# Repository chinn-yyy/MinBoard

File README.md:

# MinBoard
Ever wanted to record score for a board game and thought this pen and paper is boring. Well, I introduce you to the MinBoard, the "first" ever mini scoreboard you can take wherever you want. It features two "point" squares and one "time" square that can display how long is left and who is winning.

This design includes 3 buttons, one to add a point to HOME, one to add a point to AWAY, and 1 to reset the SCORE and TIME. Also, there is a push-dial you can adjust the TIME with, spin to change and press to confirm/start.
Any questions, bugs, inquiries, suggestions, etc. DM me on slack "@chinnyyy.".

**Photos:**

CAD:

SCHEMATIC:

PCB:

FULLY ASSEMBLED:

(not yet)

made/designed by chinnyyy.

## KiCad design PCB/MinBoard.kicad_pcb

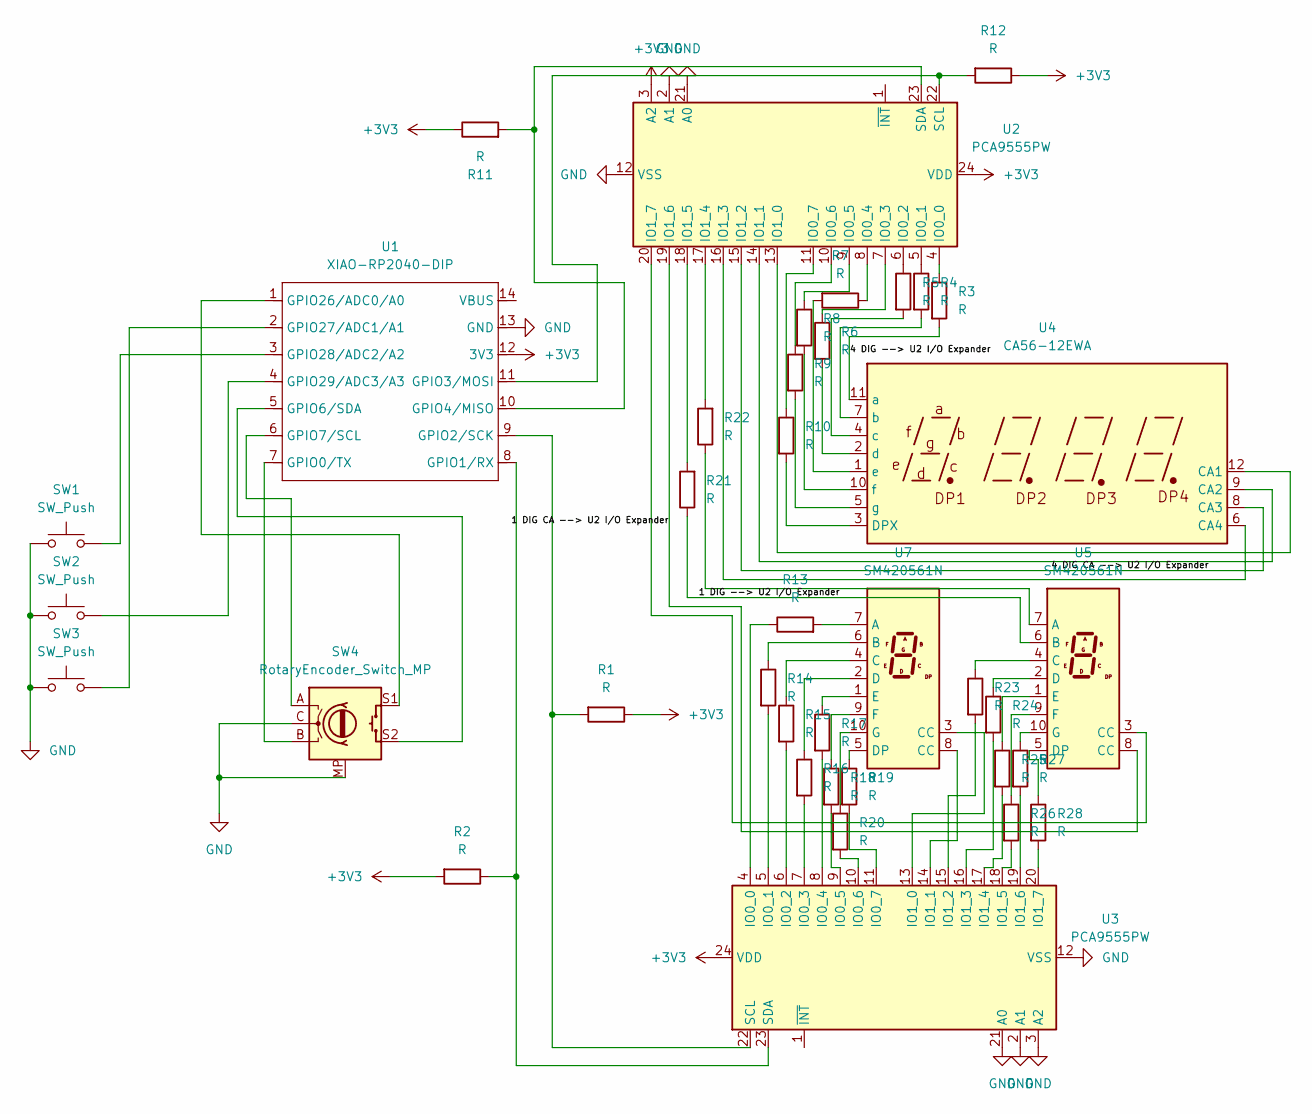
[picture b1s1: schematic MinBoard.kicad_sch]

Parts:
R1, R2, R3, R4, R5, R6, R7, R8, R9, R10, R11, R12, R13, R14, R15, R16, R17, R18, R19, R20, R21, R22, R23, R24, R25, R26, R27, R28: R; R_Axial_DIN0207_L6.3mm_D2.5mm_P7.62mm_Horizontal
SW1, SW2, SW3: SW_Push; SW_PUSH_6mm_H7.3mm
SW4: RotaryEncoder_Switch_MP; RotaryEncoder_Alps_EC11E-Switch_Vertical_H20mm
U1: XIAO-RP2040-DIP; MCU_Seeed_ESP32C3
U2, U3: PCA9555PW; TSSOP-24_4.4x7.8mm_P0.65mm
U4: CA56-12EWA
U5, U7: SM420561N; 7SegmentLED_LTS6760_LTS6780

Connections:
+3V3: R1.1, R2.2, R11.1, R12.1, U1.12 (3V3), U2.3 (A2), U2.24 (VDD), U3.24 (VDD)
/1 DIG --> U2 I/O Expander: R21.1, U5.6 (B)
/1 DIG CA --> U2 I/O Expander: U2.19 (IO1_6), U5.8 (CC)
/4 DIG --> U2 I/O Expander: R3.2, U4.11 (a)
/4 DIG CA --> U2 I/O Expander: U2.15 (IO1_2), U4.8 (CA3)
GND: SW1.1, SW2.1, SW3.1, SW4.C, SW4.MP, U1.13 (GND), U2.2 (A1), U2.12 (VSS), U2.21 (A0), U3.2 (A1), U3.3 (A2), U3.12 (VSS), U3.21 (A0)
unnamed: SW4.B, U1.7 (GPIO0/TX)
unnamed: R2.1, U1.8 (GPIO1/RX), U3.23 (SDA)
unnamed: R1.2, U1.9 (GPIO2/SCK), U3.22 (SCL)
unnamed: R12.2, U1.11 (GPIO3/MOSI), U2.22 (SCL)
unnamed: R11.2, U1.10 (GPIO4/MISO), U2.23 (SDA)
unnamed: SW4.S2, U1.5 (GPIO6/SDA)
unnamed: SW4.A, U1.6 (GPIO7/SCL)
unnamed: SW4.S1, U1.1 (GPIO26/ADC0/A0)
unnamed: SW3.2, U1.2 (GPIO27/ADC1/A1)
unnamed: SW1.2, U1.3 (GPIO28/ADC2/A2)
unnamed: SW2.2, U1.4 (GPIO29/ADC3/A3)
unnamed: R3.1, U2.4 (IO0_0)
unnamed: R4.1, U2.5 (IO0_1)
unnamed: R5.1, U2.6 (IO0_2)
unnamed: R6.1, U2.7 (IO0_3)
unnamed: R7.1, U2.8 (IO0_4)
unnamed: R8.1, U2.9 (IO0_5)
unnamed: R9.1, U2.10 (IO0_6)
unnamed: R10.1, U2.11 (IO0_7)
unnamed: U2.13 (IO1_0), U4.12 (CA1)
unnamed: U2.14 (IO1_1), U4.9 (CA2)
unnamed: U2.16 (IO1_3), U4.6 (CA4)
unnamed: R22.2, U2.17 (IO1_4)
unnamed: R21.2, U2.18 (IO1_5)
unnamed: U2.20 (IO1_7), U5.3 (CC)
unnamed: R13.1, U3.4 (IO0_0)
unnamed: R14.2, U3.5 (IO0_1)
unnamed: R15.2, U3.6 (IO0_2)
unnamed: R16.2, U3.7 (IO0_3)
unnamed: R17.2, U3.8 (IO0_4)
unnamed: R18.2, U3.9 (IO0_5)
unnamed: R20.2, U3.10 (IO0_6)
unnamed: R19.2, U3.11 (IO0_7)
unnamed: U3.13 (IO1_0), U7.3 (CC)
unnamed: U3.14 (IO1_1), U7.8 (CC)
unnamed: R23.2, U3.15 (IO1_2)
unnamed: R24.2, U3.16 (IO1_3)
unnamed: R25.2, U3.17 (IO1_4)
unnamed: R26.2, U3.18 (IO1_5)
unnamed: R27.2, U3.19 (IO1_6)
unnamed: R28.2, U3.20 (IO1_7)
unnamed: R10.2, U4.3 (DPX)
unnamed: R4.2, U4.7 (b)
unnamed: R5.2, U4.4 (c)
unnamed: R6.2, U4.2 (d)
unnamed: R7.2, U4.1 (e)
unnamed: R8.2, U4.10 (f)
unnamed: R9.2, U4.5 (g)
unnamed: R22.1, U5.7 (A)
unnamed: R23.1, U5.4 (C)
unnamed: R24.1, U5.2 (D)
unnamed: R28.1, U5.5 (DP)
unnamed: R25.1, U5.1 (E)
unnamed: R26.1, U5.9 (F)
unnamed: R27.1, U5.10 (G)
unnamed: R13.2, U7.7 (A)
unnamed: R14.1, U7.6 (B)
unnamed: R15.1, U7.4 (C)
unnamed: R16.1, U7.2 (D)
unnamed: R19.1, U7.5 (DP)
unnamed: R17.1, U7.1 (E)
unnamed: R18.1, U7.9 (F)
unnamed: R20.1, U7.10 (G)

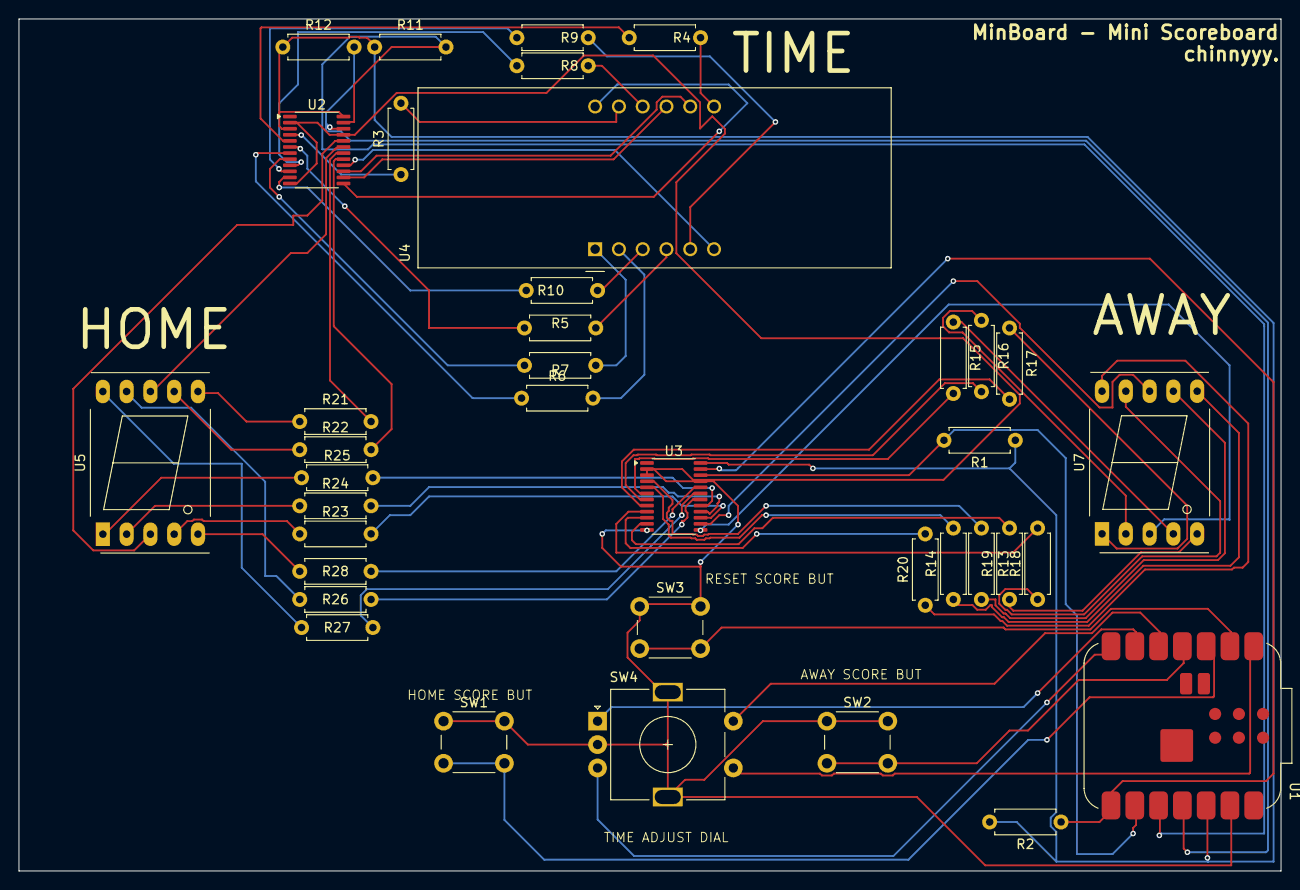
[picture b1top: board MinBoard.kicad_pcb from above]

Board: 2 copper layers, 134.8 x 91.0 mm, 38 parts (0 on the bottom side), 69 nets.

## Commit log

2026-01-17 Create CAD
2026-01-17 Create PCB
2026-01-17 Create FIRMWARE
2026-01-17 updated read.me
2026-01-17 added photos
2026-01-17 Create PLACEHOLDER
2026-01-17 Rename FIRMWARE to main.py
2026-01-18 Create Google Sheets Link
